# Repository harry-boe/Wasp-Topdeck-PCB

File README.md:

# Wasp-Topdeck-PCB

This is the pcb to simplyfy the wireing for the WASP IDEX 3d printer

The printer is a variation of the Double Dragon from zrancho

Connectors are common JST, Molex and Terminals with the exception
of a 5 pin magnetic connector for wirening the tophead USB cam and LED's

The connector can be sourced from Aliexpress here https://www.aliexpress.com/item/1005003238190621.html

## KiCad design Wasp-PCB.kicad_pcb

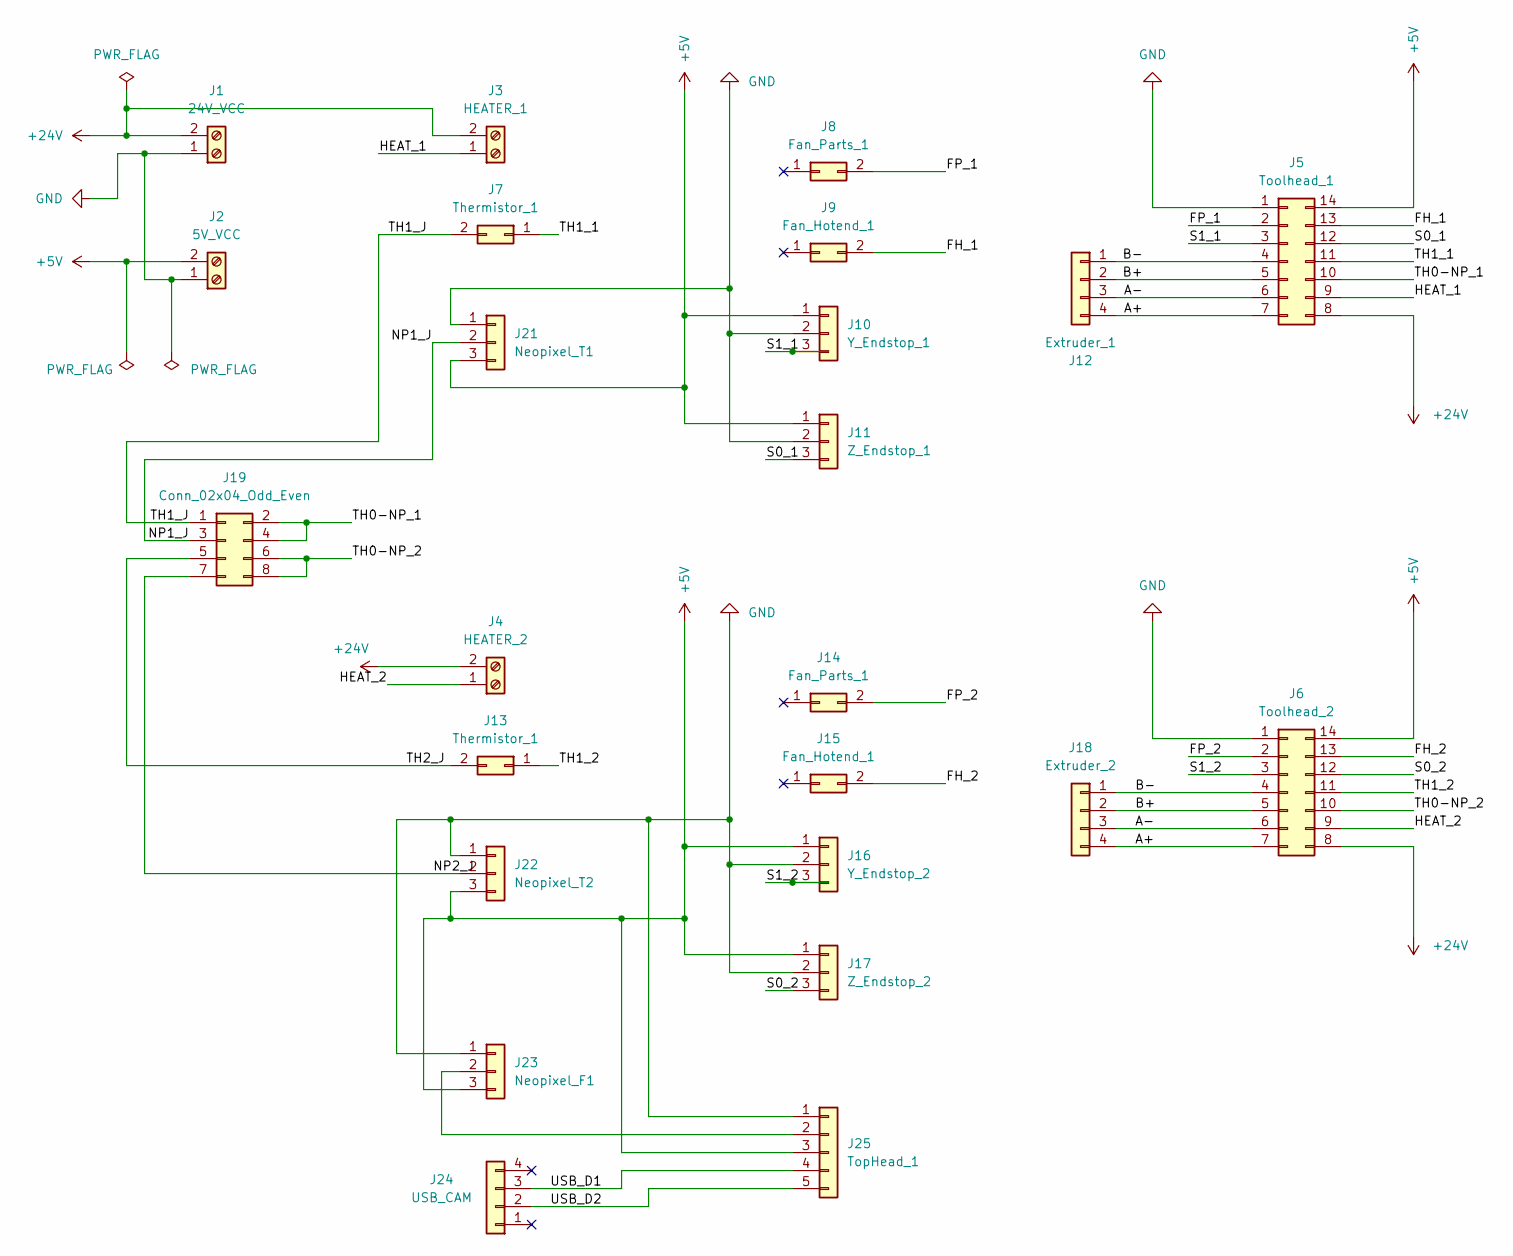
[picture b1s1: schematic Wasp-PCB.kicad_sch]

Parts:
J1: 24V_VCC; TerminalBlock_RND_205-00001_1x02_P5.00mm_Horizontal
J2: 5V_VCC; TerminalBlock_RND_205-00001_1x02_P5.00mm_Horizontal
J3: HEATER_1; TerminalBlock_RND_205-00001_1x02_P5.00mm_Horizontal
J4: HEATER_2; TerminalBlock_RND_205-00001_1x02_P5.00mm_Horizontal
J5: Toolhead_1; Molex_Micro-Fit_3.0_43045-1412_2x07_P3.00mm_Vertical
J6: Toolhead_2; Molex_Micro-Fit_3.0_43045-1412_2x07_P3.00mm_Vertical
J7, J13: Thermistor_1; JST_XH_B2B-XH-A_1x02_P2.50mm_Vertical
J8, J14: Fan_Parts_1; JST_XH_B2B-XH-A_1x02_P2.50mm_Vertical
J9, J15: Fan_Hotend_1; JST_XH_B2B-XH-A_1x02_P2.50mm_Vertical
J10: Y_Endstop_1; JST_XH_B3B-XH-A_1x03_P2.50mm_Vertical
J11: Z_Endstop_1; JST_XH_B3B-XH-A_1x03_P2.50mm_Vertical
J12: Extruder_1; JST_XH_B4B-XH-A_1x04_P2.50mm_Vertical
J16: Y_Endstop_2; JST_XH_B3B-XH-A_1x03_P2.50mm_Vertical
J17: Z_Endstop_2; JST_XH_B3B-XH-A_1x03_P2.50mm_Vertical
J18: Extruder_2; JST_XH_B4B-XH-A_1x04_P2.50mm_Vertical
J19: Conn_02x04_Odd_Even; PinHeader_2x04_P2.54mm_Vertical
J21: Neopixel_T1; JST_XH_B3B-XH-A_1x03_P2.50mm_Vertical
J22: Neopixel_T2; JST_XH_B3B-XH-A_1x03_P2.50mm_Vertical
J23: Neopixel_F1; JST_XH_B3B-XH-A_1x03_P2.50mm_Vertical
J24: USB_CAM; JST_XH_B4B-XH-A_1x04_P2.50mm_Vertical
J25: TopHead_1; Connector_Mag_05x_2.0mm

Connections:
+5V: J2.2, J5.14, J6.14, J10.1, J11.1, J16.1, J17.1, J21.3, J22.3, J23.3, J25.3
+24V: J1.2, J3.2, J4.2, J5.8, J6.8
/A+: J5.7, J6.7, J12.4, J18.4
/A-: J5.6, J6.6, J12.3, J18.3
/B+: J5.5, J6.5, J12.2, J18.2
/B-: J5.4, J6.4, J12.1, J18.1
/FH_1: J5.13, J9.2
/FH_2: J6.13, J15.2
/FP_1: J5.2, J8.2
/FP_2: J6.2, J14.2
/HEAT_1: J3.1, J5.9
/HEAT_2: J4.1, J6.9
/NP1_J: J19.3, J21.2
/NP2_J: J19.7, J22.2
/S0_1: J5.12, J11.3
/S0_2: J6.12, J17.3
/S1_1: J5.3, J10.3
/S1_2: J6.3, J16.3
/TH0-NP_1: J5.10, J19.2, J19.4
/TH0-NP_2: J6.10, J19.6, J19.8
/TH1_1: J5.11, J7.1
/TH1_2: J6.11, J13.1
/TH1_J: J7.2, J19.1
/TH2_J: J13.2, J19.5
/USB_D1: J24.3, J25.4
/USB_D2: J24.2, J25.5
GND: J1.1, J2.1, J5.1, J6.1, J10.2, J11.2, J16.2, J17.2, J21.1, J22.1, J23.1, J25.1
unnamed: J23.2, J25.2

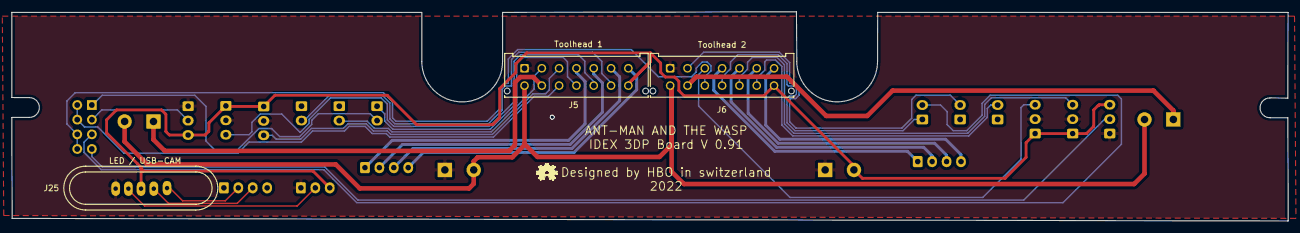
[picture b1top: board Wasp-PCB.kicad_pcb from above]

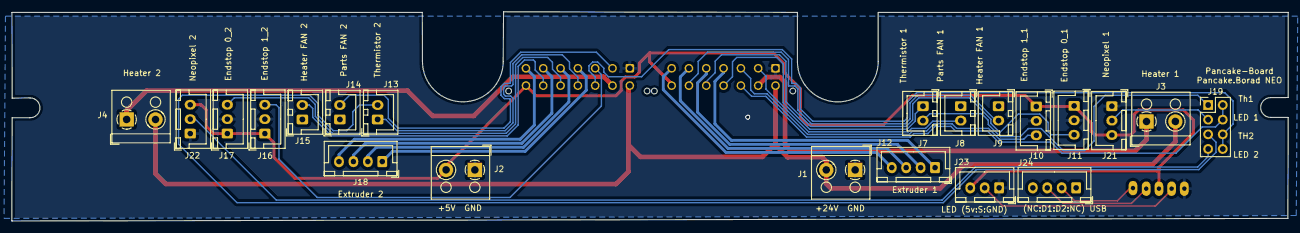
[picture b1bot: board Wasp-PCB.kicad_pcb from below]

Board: 2 copper layers, 221.2 x 36.2 mm, 24 parts (21 on the bottom side), 28 nets.

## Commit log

2022-03-08 initial upload KiCAD files
2022-03-08 KiCAD files added
2022-03-08 generated gerber files added
2022-07-03 V0.91 changed outline to create clearence for A/B belt tentioners updated readme
2022-07-03 added immages
2022-07-03 gerber files created / updated
